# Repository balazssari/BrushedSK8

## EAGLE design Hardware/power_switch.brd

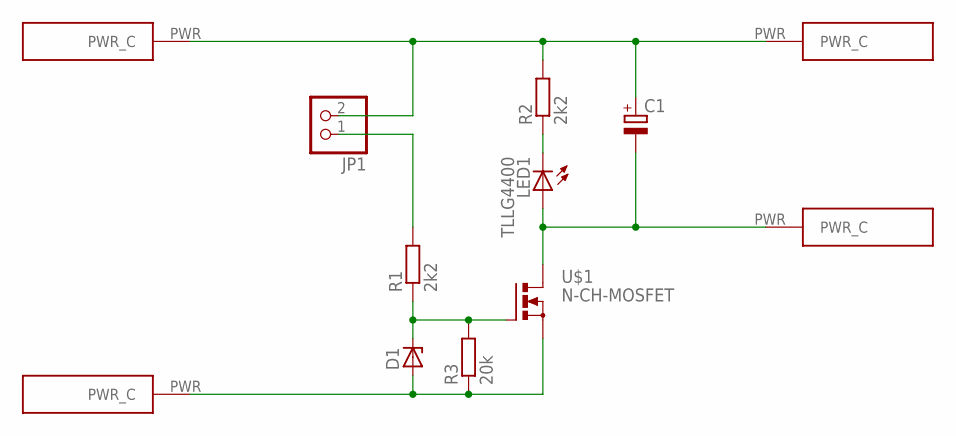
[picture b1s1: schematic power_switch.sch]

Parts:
C1: CPOL-EUE7.5-16; E7,5-16
D1: ZENER-DIODEDO41Z10; DO41Z10
JP1: PINHD-1X2; 1X02
LED1: TLLG4400; LED3MM
R1, R2: 2k2; 0204/7
R3: 20k; 0204/7
U$1: N-CH-MOSFET; TO220BV
U$2: 24V; SMD_PAD
U$3, U$4, U$5: POWERCONNECTOR; SMD_PAD

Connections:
unnamed: D1.C, R1.1, R3.2, U$1.G
unnamed: D1.A, R3.1, U$1.S, U$3.PWR
unnamed: C1.-, LED1.A, U$1.D, U$5.PWR
unnamed: LED1.K (C), R2.1
unnamed: C1.+, JP1.2, R2.2, U$2.PWR, U$4.PWR
unnamed: JP1.1, R1.2

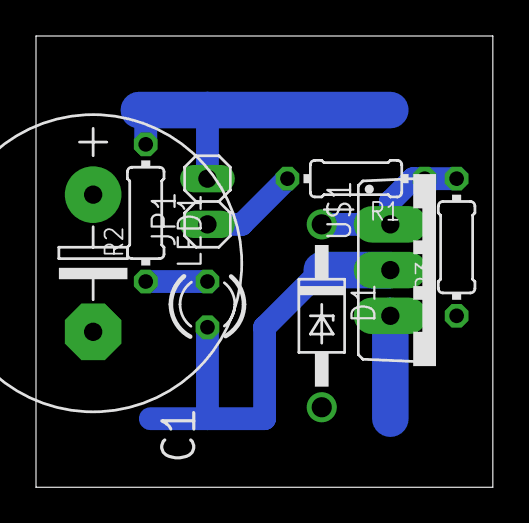
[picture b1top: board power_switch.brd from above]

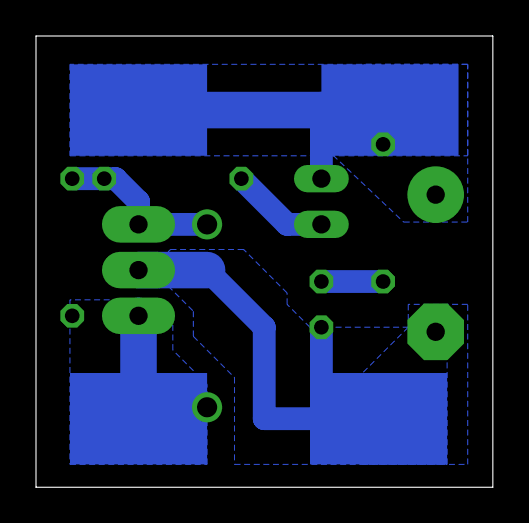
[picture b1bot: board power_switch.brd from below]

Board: 2 copper layers, 25.4 x 25.1 mm, 12 parts (4 on the bottom side), 6 nets.

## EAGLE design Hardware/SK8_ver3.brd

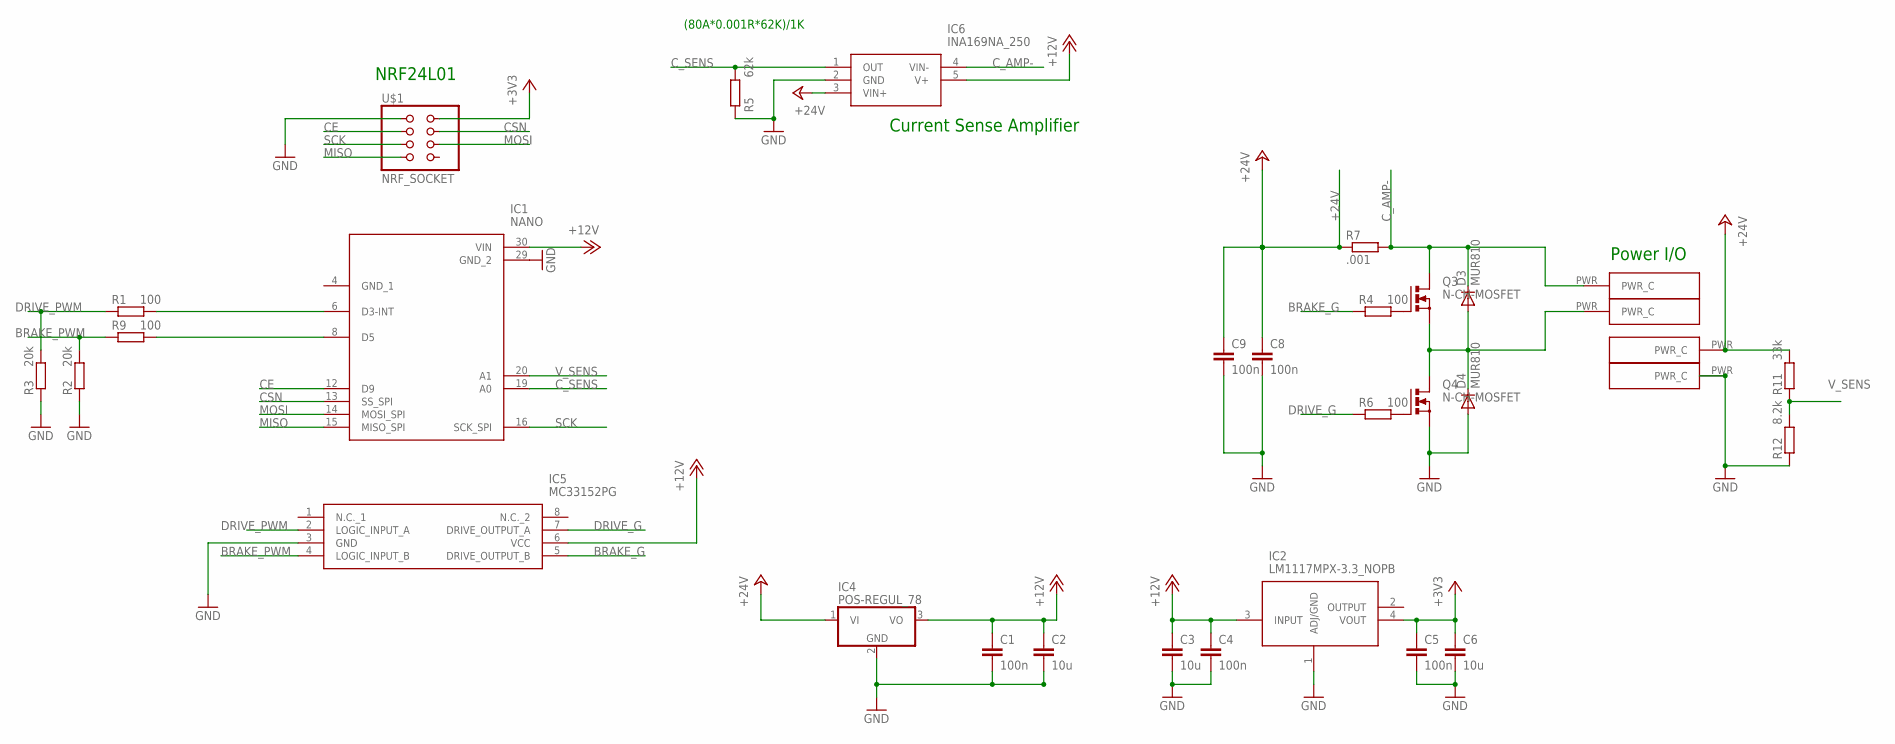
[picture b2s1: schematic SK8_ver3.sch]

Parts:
C1, C4, C5, C8, C9: 100n; C1206
C2, C3, C6: 10u; C1206
D3, D4: MUR810; TO220ACS
IC1: NANO; DIP1524W102P254L4318H762Q30N
IC2: LM1117MPX-3.3_NOPB; SOT230P700X180-4N
IC4: POS-REGUL_78; TO220V
IC5: MC33152PG; DIP794W56P254L959H533Q8N
IC6: INA169NA_250; SOT95P280X145-5N
Q3, Q4: N-CH-MOSFET; TO220BV
R1, R4, R6, R9: 100; 0204/7
R2, R3: 20k; 0204/7
R5: 62k; 0204/7
R7: .001; R2512
R11: 33k; 0204/7
R12: 8.2k; 0204/7
U$1: NRF_SOCKET; 2X04
U$2, U$3, U$4, U$5: POWERCONNECTOR; SMD_PAD

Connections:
+3V3: C5.1, C6.1, IC2.4 (VOUT), U$1.2
+12V: C1.1, C2.1, C3.1, C4.1, IC1.30 (VIN), IC2.3 (INPUT), IC4.3 (VO), IC5.6 (VCC), IC6.5 (V+)
+24V: C8.1, C9.1, IC4.1 (VI), IC6.3 (VIN+), R7.1, R11.2, U$4.PWR
BRAKE_G: IC5.5 (DRIVE_OUTPUT_B), R4.1
BRAKE_PWM: IC5.4 (LOGIC_INPUT_B), R2.2, R9.1
CE: IC1.12 (D9), U$1.3
CSN: IC1.13 (SS_SPI), U$1.4
C_AMP-: D3.C, IC6.4 (VIN-), Q3.D, R7.2, U$2.PWR
C_SENS: IC1.19 (A0), IC6.1 (OUT), R5.2
DRIVE_G: IC5.7 (DRIVE_OUTPUT_A), R6.1
DRIVE_PWM: IC5.2 (LOGIC_INPUT_A), R1.1, R3.2
GND: C1.2, C2.2, C3.2, C4.2, C5.2, C6.2, C8.2, C9.2, D4.A, IC1.29 (GND_2), IC2.1 (ADJ/GND), IC4.2 (GND), IC5.3 (GND), IC6.2 (GND), Q4.S, R2.1, R3.1, R5.1, R12.1, U$1.1, U$5.PWR
GND_1: IC1.4 (GND_1)
MISO: IC1.15 (MISO_SPI), U$1.7
MOSI: IC1.14 (MOSI_SPI), U$1.6
unnamed: IC1.6 (D3-INT), R1.2
unnamed: IC1.8 (D5), R9.2
unnamed: Q3.G, R4.2
unnamed: D3.A, D4.C, Q3.S, Q4.D, U$3.PWR
unnamed: Q4.G, R6.2
SCK: IC1.16 (SCK_SPI), U$1.5
V_SENS: IC1.20 (A1), R11.1, R12.2

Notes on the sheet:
Current Sense Amplifier
Power I/O
NRF24L01
(80A*0.001R*62K)/1K

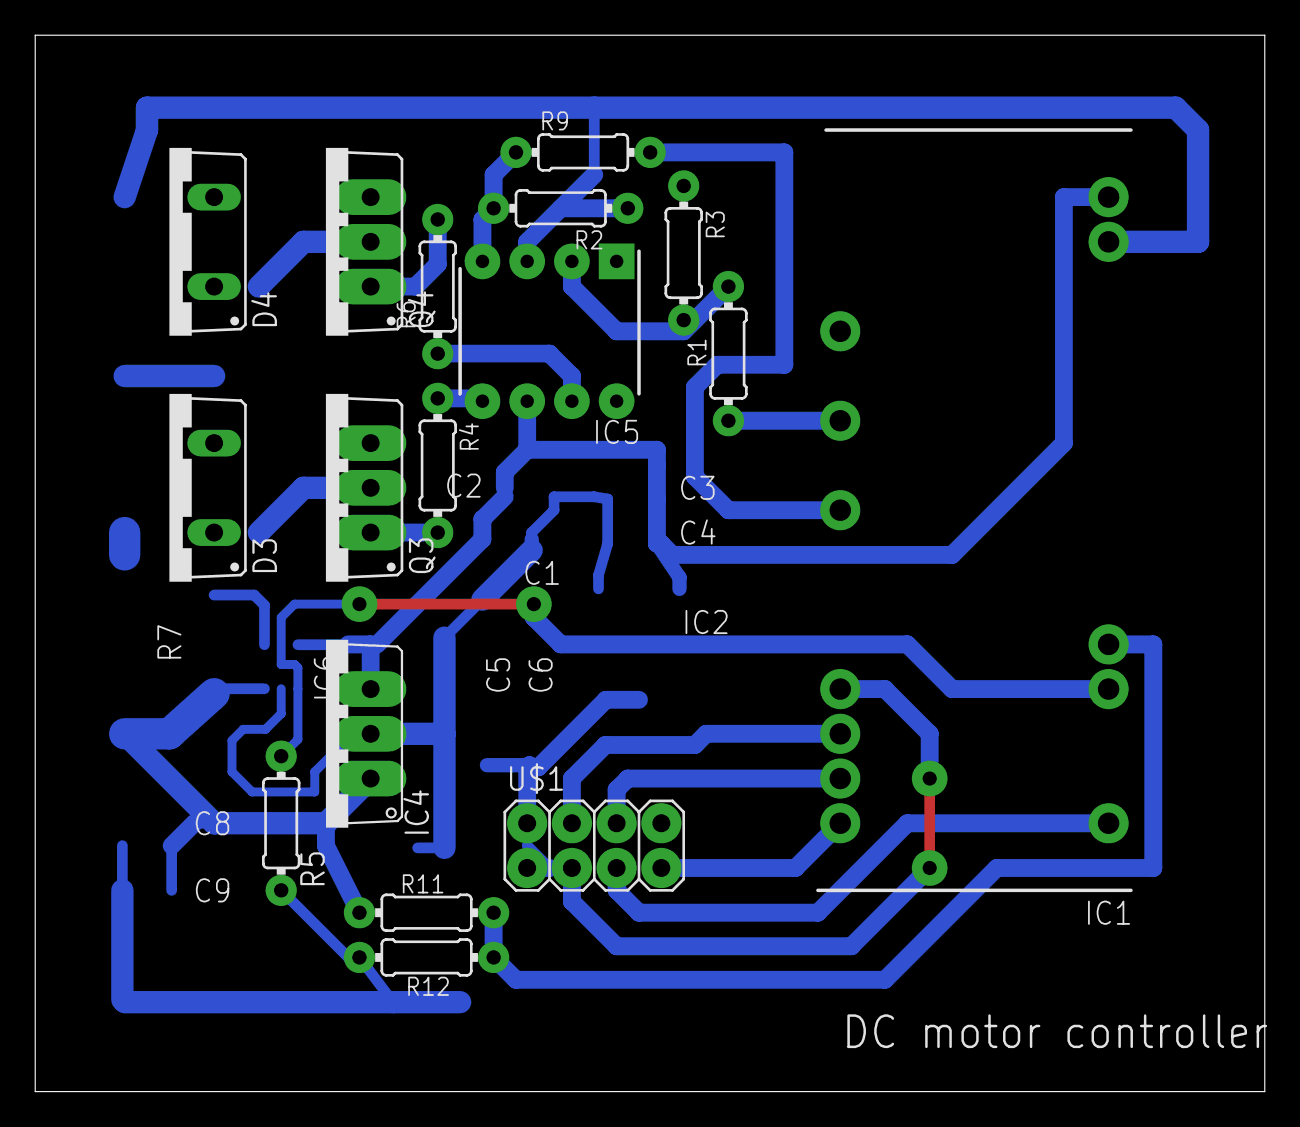
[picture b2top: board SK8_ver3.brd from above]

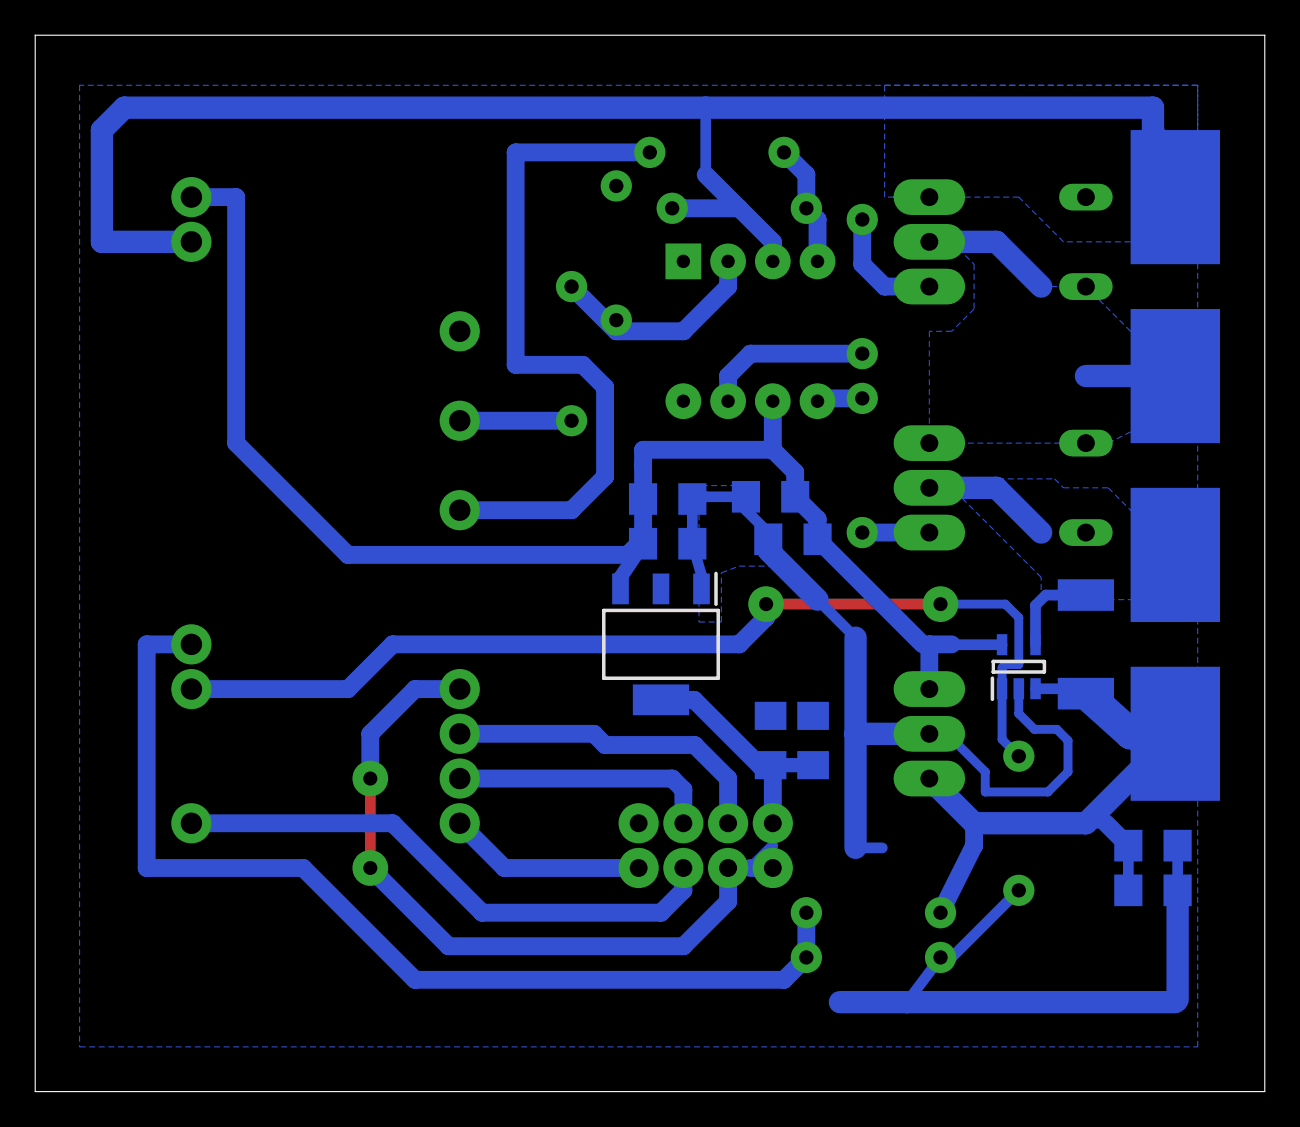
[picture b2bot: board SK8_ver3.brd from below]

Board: 2 copper layers, 69.8 x 60.0 mm, 32 parts (15 on the bottom side), 21 nets.

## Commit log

2018-09-04 v0.1
2018-09-22 v0.2
    Telemetry data now sent in ack payload, further improvements...
